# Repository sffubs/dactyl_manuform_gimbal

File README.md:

# Dactyl-Manuform-Gimbal keyboard

Why? I wanted to build something a bit different, something that I'd not seen before. I wondered what a keyboard would look like if I merged it with an RC controller, and tried using the RC gimbals as a mouse.

The result is quite fun. It's fairly space-efficient, and allows me to use the mouse with either hand. It has proximity sensors to detect when your hand is on the joystick, and turns some of the keys into mouse buttons. Haptic feedback helps to tell when you have switched layers, or long-pressed a key.

You might have noticed it has more keys on the right than the left. This is because I wanted the option to use it with [Plover](http://www.openstenoproject.org/plover/), which for a standard layout requires a minimum of 6 columns on the right, and 5 columns on the left. (I've not actually tested it with Plover, having built a [different keyboard](https://www.thingiverse.com/thing:5021950) for that in the meantime).

Fair warning: there is quite a lot of soldering involved if you want to make one:

## Components
### Keys
I picked gateron red switches and DSA keycaps, sold to me by [Mechboards](mechboards.co.uk).

### Gimbals
The twist in this design is the inclusion of a pair of joysticks. These are RC gimbals - see [here](FrSky_M9.md) for some details of how they are wired up.

### Proximity
The keyboard uses a proximity switch to detect when a hand is over the joystick, and uses this to switch the mouse buttons on. This is using an [APDS-9660](https://www.sparkfun.com/products/12787) sensor & breakout board which is glued to the underside of the case (it's the purple circuit board visible under the corner of the gimbal).

Here it is working:

The proximity sensor looks up through the little square hole next to the gimbal, so your hand needs to be somewhere over that hole for it to activate:

It will trigger unexpectedly if you get hair over that hole, so I advise you to keep your cat away from it.

### Controller
Originally this was designed to work with two [Pro Micro](https://www.sparkfun.com/products/12640) controllers, but these didn't really have enough flash for the QMK features I wanted.

So I used a beefier board that I was familiar with: the [Teensy 3.2](https://www.hobbytronics.co.uk/teensy-v32), which has been really good to me before. However, it turns out that QMK only sort-of supports the Teensy, so I had a lot of trouble getting it to work reliably.

In the end, I gave up, and swapped to a pair of [STM32F401CCU6 "Black pill"](https://stm32-base.org/boards/STM32F401CCU6-WeAct-Black-Pill-V1.2.html) controllers. These work flawlessly with QMK, though I did manage to kill two boards during assembly, and I'm not quite sure how.

In any case, the swap from the original 5v board to a 3.3v one meant that a level-shifter had to be added between the board and the I2C and LED lines on the breakout board.

Here's how the blackpill controller is wired:

B10 should be wired to 3V3 on the left-hand half, and to GND on the right-hand half.

Remember that TX1 on the left-hand half needs to be connected to RX1 on the right-hand half, and vice-versa.

### Haptic
I wanted to try getting some haptic feedback from the keyboard, for example when using mod-taps, or when switching to/from mouse mode. QMK has support for the [DRV2605L](https://learn.adafruit.com/adafruit-drv2605-haptic-controller-breakout) driver built in, so I used this.

I picked a linear resonant actuator to use with it, the Jinlong G0832012. Not for any highly specific reason; it was easily available and looked like roughly the right thing.

### LEDs & per-key PCBs
Per-key RGB LEDs are the cornerstone of a fancy mechanical keyboard! I had to have them. To try and keep things tidy, I used [Amoeba Royale](https://github.com/mtl/keyboard-pcbs/tree/master/amoeba-royale) per-key PCBs, printed for me by [Aisler](https://aisler.net). I got a bunch of SK6812 mini 3535 LEDs to to go with them, along with kailh hotswap sockets, and some small signal diodes.

Honestly, they were still quite painful to use. The holes in the PCB had to be filed out before the LEDs would fit in them, and the LED casings would melt if the soldering iron was on them for more than half a second. I had a couple of PCBs that were faulty also.

Here was my method for soldering them:
- Sit the LED in the hole
- Spread some flux over the back of the LED
- For each terminal
	- Put some solder on the PCB pad
	- Dag it onto the LED. Hopefully you will get a little solder bridge form
- Try once for each pad, and if it didn't work, leave it for a couple of minutes to cool before you try again.
- Repeat until all connections are made, then test the PCB.

However, once the whole lot was wired up, they do look quite tidy. The PCBs are not secured to the case, it seems to be enough just to press-fit them onto the back of the keys.

### Split communication
The two halves communicate through a TRRS connector. However, this just provides serial communications and a common ground wire - I left the 5v wire unconnected. Both of the halves need to be connected to the host computer over USB. This is for two reasons:
- Each half can send its own mouse events, which simplifies things
- I think the power draw for the whole keyboard might exceed 500ma - certainly I had some problems trying to power the whole thing from a single USB port

### OLED
I bought a pair of "OLED screens" from Mechboards, because of course I wanted my keyboard to have a screen! Actually this turned out to be a really helpful debugging tool, and I ended up printing a lot of diagnostic information to the OLED screen. I suspect they are SSD1306 128x32 screens, since they worked in QMK without any modifications.

## Daughterboard PCB
There are a lot of connections in this keyboard: the haptic breakout board, proximity board, OLED, LED, gimbals, TRRS connection. Wiring all of these directly to the controller would be difficult.

To simplify things, I designed a PCB to hold all of these connections. It also contains a 3.3v regulator to drive the ADPS9660 board, from back when the whole system was designed to run on 5v.

Originally the SCL, SDA, and LED connections on the left were meant to go straight to pins on the pro micro controller. However, when using this with a blackpil controller, you will need to use a [level shifter](https://learn.sparkfun.com/tutorials/bi-directional-logic-level-converter-hookup-guide/all) to convert between 3.3v and 5v.

Here are the sources:
- [dactyl-manuform-gimbal.kicad_pcb](dactyl-manuform-gimbal.kicad_pcb)
- [dactyl-manuform-gimbal.pro](dactyl-manuform-gimbal.pro)
- [dactyl-manuform-gimbal.sch](dactyl-manuform-gimbal.sch)

I had mine manufactured by [Aisler](https://aisler.net/).

You will also need these parts to make up the board:
- Q3: 2N3904 TO-92
- R6 & R7: 1k resistor
- R2, R3, R4, R5: 10k resistor
- Q1 & Q2: BS170 TO-92
- R1: 470R resistor
- J5 & J6: JST_PH_B3B header
- AMS1117 3.3v voltage regulator
- Adafruit DRV2506L haptic driver

## Geometry
The geometry was generated using a fork of Joshua Shreve's dactyl-keyboard generator:

https://github.com/sffubs/dactyl-keyboard/tree/gimbal

I custom-designed some controller trays to fit:

https://cad.onshape.com/documents/eb5f1e8bc035539a3b22c66d/w/b0de5830ef436e9c93686258/e/9e4ae3f698d1b142e7089f96?renderMode=0&uiState=621a5917d956b2473540e545

This for the right-hand keyboard - you will need to print the mirror image for the left-hand keyboard.

The final files I used are here:
- [DM_left_final.step](DM_left_final.step)
- [DM_left_final.stl](DM_left_final.stl)
- [DM_left_plate_final.stp](DM_left_plate_final.stp)
- [DM_left_plate_final.stl](DM_left_plate_final.stl)
- [DM_right_final.step](DM_right_final.step)
- [DM_right_final.stl](DM_right_final.stl])
- [DM_right_plate_final.step](DM_right_plate_final.step)
- [DM_right_plate_final.stl](DM_right_plate_final.stl)
- [Controller_tray.stl](Controller_tray.stl)
- [DM_OLED_clip.stl](DM_OLED_clip.stl)

## Printing
I printed this on my Ender 3, using Prusament Galaxy Black PLA filament, with a 0.4mm nozzle at 0.2mm resolution. I used tree-style supports, which much reduced the time and plastic required.

## Firmware

The keyboard runs on QMK, and the firmware can be found here:

https://github.com/sffubs/qmk_firmware/tree/master/keyboards/handwired/dactyl_manuform_gimbal

Build using 

`qmk -kb handwired/dactyl_manuform_gimbal -km default`

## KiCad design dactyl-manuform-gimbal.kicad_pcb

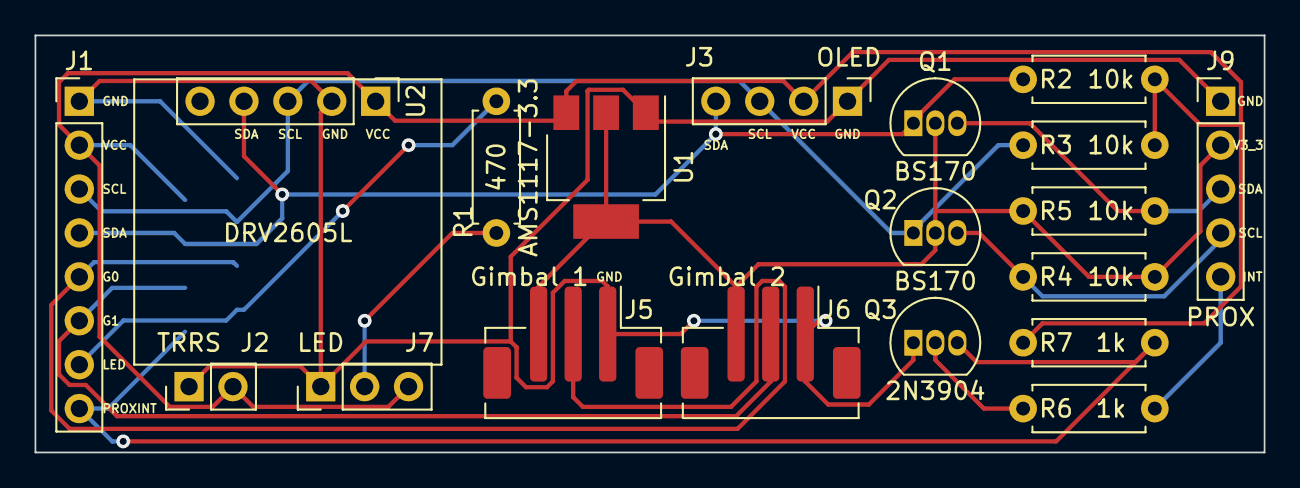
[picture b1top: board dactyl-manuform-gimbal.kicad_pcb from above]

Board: 2 copper layers, 71.1 x 24.1 mm, 20 parts (1 on the bottom side), 14 nets.

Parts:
J1: Arduino; PinHeader_1x08_P2.54mm_Vertical
J2: TRRS; PinHeader_1x02_P2.54mm_Vertical
J3: OLED; PinHeader_1x04_P2.54mm_Vertical
J5: Gimbal 1; JST_PH_B3B-PH-SM4-TB_1x03-1MP_P2.00mm_Vertical
J6: Gimbal 2; JST_PH_B3B-PH-SM4-TB_1x03-1MP_P2.00mm_Vertical
J7: LED; PinHeader_1x03_P2.54mm_Vertical
J8: Debug; PinHeader_1x08_P1.27mm_Vertical_SMD_Pin1Left
J9: PROX; PinHeader_1x05_P2.54mm_Vertical
Q1, Q2: BS170; TO-92_Inline
Q3: 2N3904; TO-92_Inline
R1: 470; R_Axial_DIN0207_L6.3mm_D2.5mm_P7.62mm_Horizontal
R2, R3, R4, R5: 10k; R_Axial_DIN0207_L6.3mm_D2.5mm_P7.62mm_Horizontal
R6, R7: 1k; R_Axial_DIN0207_L6.3mm_D2.5mm_P7.62mm_Horizontal
U1: AMS1117-3.3; SOT-223-3_TabPin2
U2: DRV2605L; DRV2605L_Adafruit

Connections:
/G0: J1.5, J5.2, J8.5
/G1: J1.6, J6.2, J8.6
/GND: J1.1, J2.1, J3.1, J5.1, J6.1, J7.1, J8.1, J9.1, Q3.1, U1.1, U2.2
/INT: J1.8, J8.8, Q3.3, R7.2
/INT3_3: J9.5, R6.2
/LED: J1.7, J8.7, R1.1
/SCL: J1.3, J3.3, J8.3, Q2.1, R3.1, U2.3
/SCL3_3: J9.4, Q2.3, R5.1
/SDA: J1.4, J3.4, J8.4, Q1.1, R2.1, U2.4
/SDA3_3: J9.3, Q1.3, R4.1
/V3_3: J5.3, J6.3, J9.2, Q1.2, Q2.2, R4.2, R5.2, U1.2
/VCC: J1.2, J2.2, J3.2, J7.3, J8.2, R2.2, R3.2, R7.1, U1.3, U2.1
unnamed: J7.2, R1.2
unnamed: Q3.2, R6.1

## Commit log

2022-01-28 Initial commit of details about how I built this keyboard.
2022-01-28 Switched to standard Markdown syntax.
2022-01-28 Added details of per-key PCBs.
2022-01-28 Added details on split commmunications.
2022-01-28 Added an introduction.
2022-01-28 Added controller pinout.
2022-01-28 Added note on keycaps.
2022-01-28 Formatting tweak.
2022-01-28 Added method for soldering LEDs.
2022-01-28 Added gif showing the proximity sensor working.
2022-01-28 Added picture of underneath.
2022-01-28 Trying to fix broken link.
2022-01-28 Another attempt at fixing the broken link.
2022-01-28 Another attempt at fixing this broken link.
2022-01-28 Added picture showing proximity sensor location.
2022-01-29 Added details of OLED screens.
2022-01-29 Fixed typo.
2022-02-26 Added controller tray.
2022-03-13 Added OLED clip geometry.
